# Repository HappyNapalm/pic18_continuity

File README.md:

# pic18_continuity
Repo for testing continuity

## TODO
* Hammer out the firmware.
* Set timer 3 up as the IO test timer. Make it 8 bits.
* Make footprint for push button.

##License
* Free for non commerical use.
* Remakes and spin offs must give credit to this project.

~Assemble boards to verify designs~

~Verify RJ45~

~Order Alpha Run~

~Get dimensions for DB9 connectors~

~Do battery footprint~

~Learn how to submit multiple boards in one design for vendor~

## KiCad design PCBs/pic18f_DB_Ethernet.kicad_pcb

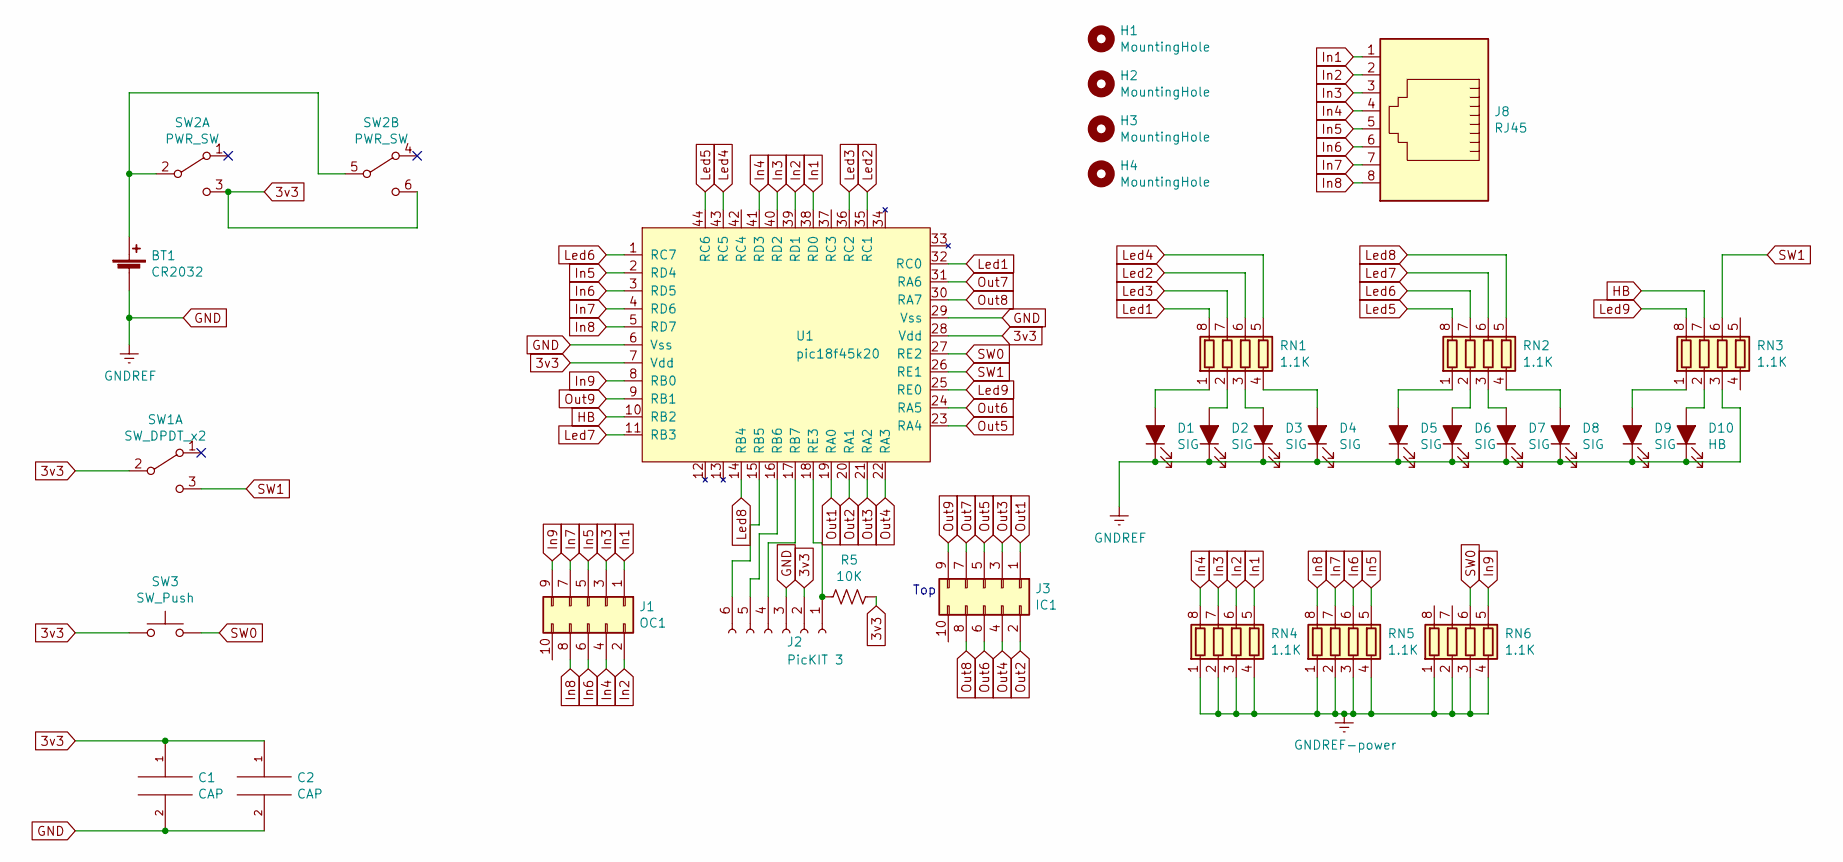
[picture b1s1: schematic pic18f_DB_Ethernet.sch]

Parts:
BT1: CR2032; BAT-HLD-001
C1, C2: CAP; C_0805_2012Metric
D1, D2, D3, D4, D5, D6, D7, D8, D9: SIG; LED_0603_1608Metric
D10: HB; LED_0603_1608Metric
H1, H2, H3, H4: MountingHole; MountingHole_3.2mm_M3
J1: OC1; PinHeader_2x05_P2.54mm_Vertical
J2: PicKIT 3; PinHeader_1x06_P2.54mm_Vertical
J3: IC1; PinHeader_2x05_P2.54mm_Vertical
J8: RJ45; RJ45_Amphenol_54602-x08_Horizontal
R5: 10K; R_0603_1608Metric
RN1, RN2, RN3, RN4, RN5, RN6: 1.1K; R_Array_Concave_4x0603
SW1: SW_DPDT_x2; JS202011SCQN
SW2: PWR_SW; JS202011SCQN
SW3: SW_Push; SPST_Button_FSM2JRT
U1: pic18f45k20; LQFP-44_10x10mm_P0.8mm

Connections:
3v3: C1.1, C2.1, J2.2, R5.1, SW1.2 (B), SW2.3 (C), SW2.6 (C), SW3.1, U1.7 (Vdd), U1.28 (Vdd)
HB: RN3.7 (R2.2), U1.10 (RB2)
In1: J1.1, J8.1, RN4.5 (R4.2), U1.38 (RD0)
In2: J1.2, J8.2, RN4.6 (R3.2), U1.39 (RD1)
In3: J1.3, J8.3, RN4.7 (R2.2), U1.40 (RD2)
In4: J1.4, J8.4, RN4.8 (R1.2), U1.41 (RD3)
In5: J1.5, J8.5, RN5.5 (R4.2), U1.2 (RD4)
In6: J1.6, J8.6, RN5.6 (R3.2), U1.3 (RD5)
In7: J1.7, J8.7, RN5.7 (R2.2), U1.4 (RD6)
In8: J1.8, J8.8, RN5.8 (R1.2), U1.5 (RD7)
In9: J1.9, RN6.5 (R4.2), U1.8 (RB0)
Led1: RN1.8 (R1.2), U1.32 (RC0)
Led2: RN1.6 (R3.2), U1.35 (RC1)
Led3: RN1.7 (R2.2), U1.36 (RC2)
Led4: RN1.5 (R4.2), U1.43 (RC5)
Led5: RN2.8 (R1.2), U1.44 (RC6)
Led6: RN2.7 (R2.2), U1.1 (RC7)
Led7: RN2.6 (R3.2), U1.11 (RB3)
Led8: RN2.5 (R4.2), U1.14 (RB4)
Led9: RN3.8 (R1.2), U1.25 (RE0)
unnamed: BT1.1 (+), SW2.2 (B), SW2.5 (B)
unnamed: D1.2 (A), RN1.1 (R1.1)
unnamed: D2.2 (A), RN1.2 (R2.1)
unnamed: D3.2 (A), RN1.3 (R3.1)
unnamed: D4.2 (A), RN1.4 (R4.1)
unnamed: D5.2 (A), RN2.1 (R1.1)
unnamed: D6.2 (A), RN2.2 (R2.1)
unnamed: D7.2 (A), RN2.3 (R3.1)
unnamed: D8.2 (A), RN2.4 (R4.1)
unnamed: D9.2 (A), RN3.1 (R1.1)
unnamed: D10.2 (A), RN3.2 (R2.1)
unnamed: J2.1, R5.2, U1.18 (RE3)
unnamed: J2.4, U1.17 (RB7)
unnamed: J2.5, U1.16 (RB6)
unnamed: J2.6, U1.15 (RB5)
Out1: J3.1, U1.19 (RA0)
Out2: J3.2, U1.20 (RA1)
Out3: J3.3, U1.21 (RA2)
Out4: J3.4, U1.22 (RA3)
Out5: J3.5, U1.23 (RA4)
Out6: J3.6, U1.24 (RA5)
Out7: J3.7, U1.31 (RA6)
Out8: J3.8, U1.30 (RA7)
Out9: J3.9, U1.9 (RB1)
SW0: RN6.6 (R3.2), SW3.2, U1.27 (RE2)
SW1: RN3.6 (R3.2), SW1.3 (C), U1.26 (RE1)

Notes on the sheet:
Top

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
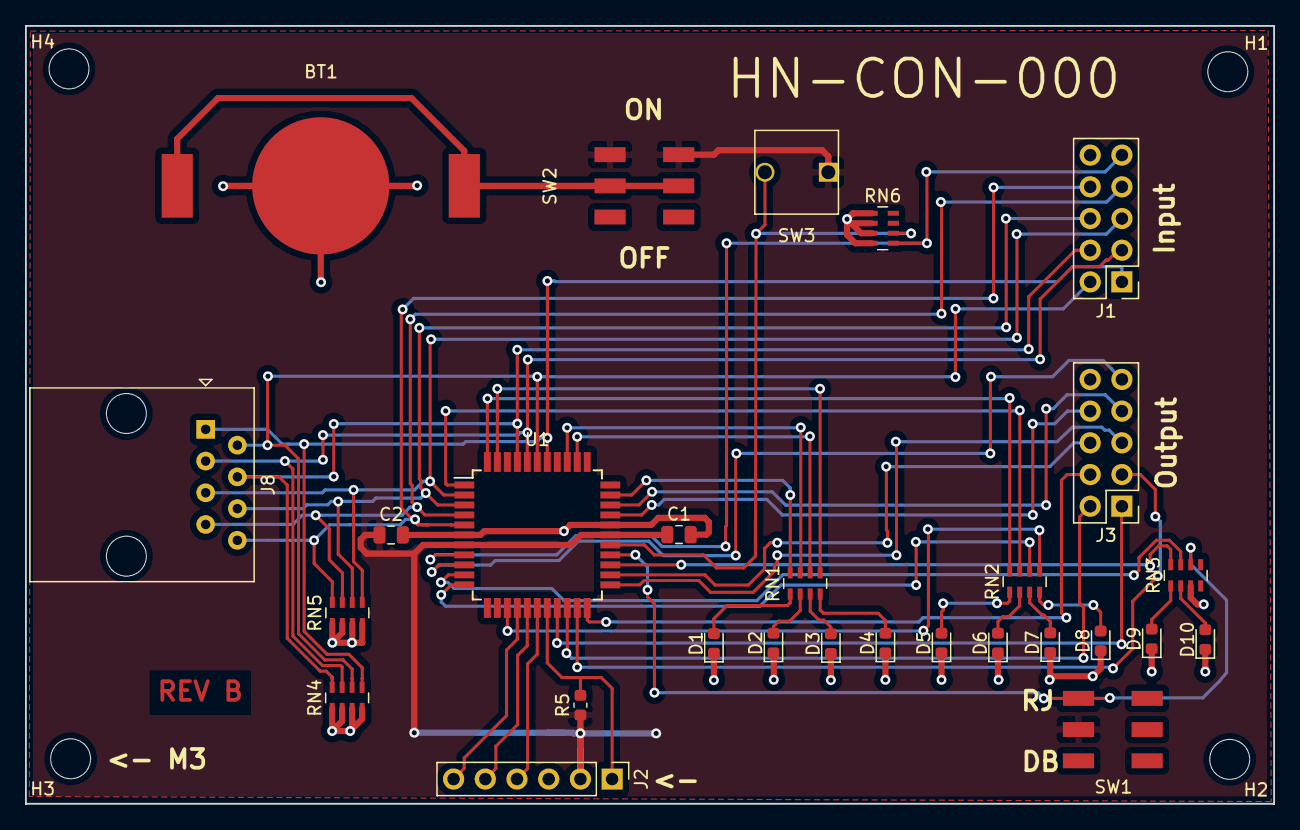
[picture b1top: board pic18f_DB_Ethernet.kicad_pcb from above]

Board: 2 copper layers, 100.0 x 62.3 mm, 32 parts (0 on the bottom side), 47 nets.

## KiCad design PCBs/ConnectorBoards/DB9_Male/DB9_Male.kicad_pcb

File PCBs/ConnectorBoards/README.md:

This dir is to contain the modular boards that the central board can connect to.

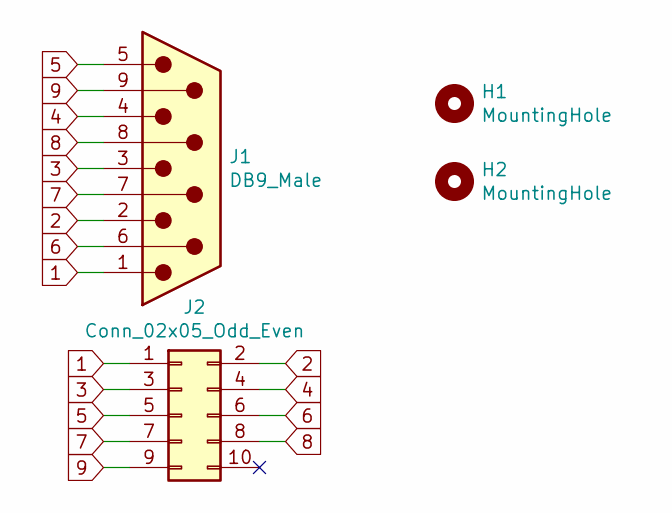
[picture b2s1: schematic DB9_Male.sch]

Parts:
H1, H2: MountingHole; MountingHole_3.2mm_M3
J1: DB9_Male; DSUB-9_Male_Horizontal_P2.77x2.84mm_EdgePinOffset4.94mm_Hou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
J2: Conn_02x05_Odd_Even; PinHeader_2x05_P2.54mm_Vertical

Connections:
1: J1.1, J2.1
2: J1.2, J2.2
3: J1.3, J2.3
4: J1.4, J2.4
5: J1.5, J2.5
6: J1.6, J2.6
7: J1.7, J2.7
8: J1.8, J2.8
9: J1.9, J2.9

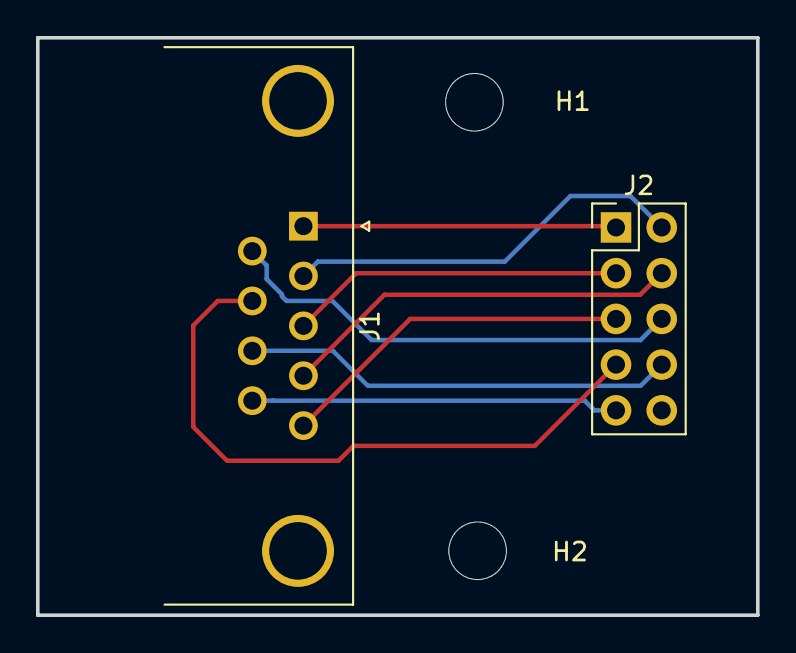
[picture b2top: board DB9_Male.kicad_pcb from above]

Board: 2 copper layers, 40.0 x 32.1 mm, 4 parts (0 on the bottom side), 9 nets.

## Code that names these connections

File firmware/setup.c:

#include <stdio.h>
//#include <stdlib.h>
#include <xc.h>
#include <htc.h>
#include "setup.h"
#include "leds.h"

//@About set GPIO table item to boolean
void set_IO (struct gstGPIO *IO, unsigned char item,unsigned char bValue)
{
    volatile unsigned char *ucLocal;
    ucLocal = IO[item].port;
    if (bValue)
    {
        *ucLocal |= (1 << IO[item].pin);
    }
    else
    {
        *ucLocal &= ~(1 << IO[item].pin);
    }
}

//@About get the state of an item from a GPIO table
unsigned char get_IO (struct gstGPIO *IO, unsigned char item)
{
    return (unsigned char)((*IO[item].port >> IO[item].pin) & 0x01);
}

struct gstGPIO astInputs[] = {
    {&PORTD, 0},
    {&PORTD, 1},
    {&PORTD, 2},
    {&PORTD, 3},
    {&PORTD, 4},
    {&PORTD, 5},
    {&PORTD, 6},
    {&PORTD, 7},
    {&PORTB, 0},
};

struct gstGPIO astOutputs[] = {
    {&LATA, 0},
    {&LATA, 1},
    {&LATA, 2},
    {&LATA, 3},
    {&LATA, 4},
    {&LATA, 5},
    {&LATA, 6},
    {&LATA, 7},
    {&LATB, 1},
};

void IO_setup (void)
{
  TRISA = 0x00;           //Outputs
  TRISC = 0x00;           //LEDS
  TRISBbits.RB0 = 1;      //In9
  TRISBbits.RB1 = 0;      //Out9
  TRISBbits.RB2 = 0;      //HB
  TRISBbits.RB3 = 0;      //LED7
  TRISBbits.RB4 = 0;      //LED8
  TRISD = 0xFF;           //Inputs
  TRISEbits.RE0 = 0;      //LED9
  TRISEbits.RE1 = 1;      //Switch 1A
  TRISEbits.RE2 = 1;      //Switch 1B
}


void Timer_and_Interrupt_setup (void)
{
    //Let this timer run as a free running timer
    
    //16 bits. 1:64 prescaler. Internal. 1 tick is 8us
    T0CON = 0b10010101;
    //INTCONbits.TMR0IE = 1;
    
    //8Mhz timer. Internal
    OSCCON = 0b01100111;
    
    
    T3CON = 0b00000101;
}

void clr_Timer (void)
{
    TMR0H = 0;
    TMR0L = 0;
}

void clr_Timer3 (void)
{
    TMR3H = 0;
    TMR3L = 0;
}

void __interrupt() ISR()
{
    if(TMR0IF)
    {
        TMR0IF = 0;
        clr_Timer();
        HB = !HB;
        gbTick++;
    }
    if(TMR3IF)
    {
        TMR3IF = 0;
        clr_Timer3();
        guc_3_Tick++;
        gucTestBit++;
    }
}

inline volatile unsigned short get_Time(void)
{
    return ((unsigned short)(TMR0H << 8) | TMR0L);
}

//@About: Checks with the free running timer
unsigned char bTimeUp(
                        unsigned short StartTime,
                        /*unsigned char StartOverFlowCount,*/
                        unsigned short Period
                     )
{
    unsigned char b = 0;
    unsigned short CurrentTime = get_Time();
    
    if (CurrentTime < StartTime)
    {
//        if(StartOverFlowCount > gbTick)
//        {
            if(((0xFFFF - StartTime) + CurrentTime) >= Period)
                {
                    b = 1;
                }
//        }
    }
    else if (CurrentTime - StartTime >= Period)
    {
        b = 1;
    }
    return b;
}

void setup(void)
{
    INTCONbits.GIE = 0;
    IO_setup();
    //clr_Timer();
    HB = 0;
    Timer_and_Interrupt_setup();
    INTCONbits.GIE = 1;
    INTCONbits.PEIE = 1;
    INTCONbits.TMR0IE = 1;
    T0CONbits.TMR0ON = 1;
    T3CONbits.TMR3ON = 0;
    all_LEDs();
    
    
}

#define HB_PERIOD 10000
void heartbeat(void)
{
    static unsigned char nbFirst;
    static unsigned short uwStartTime;
    static unsigned char ucOverFlow;
    //unsigned short uwCurrentTime = get_Time();
    if(!nbFirst)
    {
        uwStartTime = get_Time();
        ucOverFlow = gbTick;
        nbFirst = 1;
    }
    else
    {
        if(bTimeUp(uwStartTime,/*ucOverFlow,*/HB_PERIOD))
        {
            HB = !HB;
        }
    }
}

void compare_IO(unsigned char TargetBit)
{
    unsigned char bOutput = get_IO(astOutputs,TargetBit);
    unsigned char bInput  = get_IO(astInputs ,TargetBit);
    set_IO(astLEDs,TargetBit,(bOutput == bInput==1));
    
}

void testing(unsigned char TargetBit)
{
    static unsigned char b;
    static unsigned char ucLocalTicks;
    static unsigned char nbFirst;
    if(!nbFirst)
    {
        b = 1;
        nbFirst = 1;
        ucLocalTicks = guc_3_Tick;
        T3CONbits.TMR3ON = 1;   //Start the timer
    }
    if(ucLocalTicks != guc_3_Tick)
    {
        T3CONbits.TMR3ON = 0;
        b = 0;
        nbFirst = 0;
    }
    set_IO(astOutputs,TargetBit,b);
    compare_IO(TargetBit);
}

//# Potential EEPROM code below #//

// unsigned char read_eeprom(unsigned char ucAddress)
// {
//   unsigned char Data;
//   EEADR = ucAddress;       // Write The Address From Which We Wonna Get Data
//   EECON1bits.EEPGD = 0;  // Cleared To Point To EEPROM Not The Program Memory
//   EECON1bits.RD = 1;     // Start The Read Operation
//   Data = EEDATA;         // Read The Data
//   return (Data);

// }

// void write_eeprom(unsigned char ucAddress, unsigned char ucData)
// {
//   while(EECON1bits.WR);  // Waits Until Last Attempt To Write Is Finished
//   EEADR = ucAddress;       // Writes The Addres To Which We'll Wite Our Data
//   EEDATA = ucData;         // Write The Data To Be Saved
//   EECON1bits.EEPGD = 0;  // Cleared To Point To EEPROM Not The Program Memory
//   EECON1bits.WREN = 1;   // Enable The Operation !
//   INTCONbits.GIE = 0;    // Disable All Interrupts Untill Writting Data Is Done
//   EECON2 = 0x55;         // Part Of Writing Mechanism..
//   EECON2 = 0xAA;         // Part Of Writing Mechanism..
//   EECON1bits.WR = 1;     // Part Of Writing Mechanism..
//   INTCONbits.GIE = 1;    // Re-Enable Interrupts
//   EECON1bits.WREN = 0;   // Disable The Operation
//   EECON1bits.WR = 0;     // Ready For Next Writting Operation             
// }

// void reset_eeprom(void)
// {
//     unsigned char byte_count;
//     for(byte_count = 0; byte_count < 100; byte_count++)
//     {
//         write_eeprom(byte_count,0xff);
//     }
// }

// void HEX_2_LED(unsigned char EEPROM_MEM_ADDRESS)
// {
//     unsigned char LED_1;
//     unsigned char LED_2;
//     LED_1 = EEPROM_MEM_ADDRESS & 0x0F;
//     LED_2 = (EEPROM_MEM_ADDRESS & 0xF0 >> 4);
//     LED_Output_Single(LED_1,1);
//     LED_Output_Single(LED_2,1);
// }

// //On power up make it so you cycle through the EEPROM from 0-95 (six passes)
// //Read until you find one that mets the following criteria:
// //  (1) Not 0xFF
// //  (2) Highest value found
// //  (3) Then increment the value
// //  (4) Read the value and modulate by 16 to get the animation timer.
// //  (5) Assume that 0xFF at address 0 means we have restarted
// //  (6) If at address 95, then we can reset.


// void start_up(void)
// {
//     unsigned char ucDataOut = 0;
//     unsigned char ucValid = 0;
    
//     ucDataOut = read_eeprom(0x0A);
//     if(ucDataOut > 7)
//     {
//         ucDataOut = 0;
//     }
//     gucAnimationState = ucDataOut;
//     write_eeprom(0x0A,(ucDataOut+1));
// }

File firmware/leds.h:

/* 
 * File:   leds.h
 * Author: church
 *
 * Created on April 5, 2020, 5:24 PM
 */

#ifndef LEDS_H
#define	LEDS_H

#ifdef	__cplusplus
extern "C" {
#endif




#ifdef	__cplusplus
}
#endif

//Macros
#define LED1  LATCbits.LC0
#define LED2  LATCbits.LC2
#define LED3  LATCbits.LC1
#define LED4  LATCbits.LC5
#define LED5  LATCbits.LC6
#define LED6  LATCbits.LC7
#define LED7  LATBbits.LB3
#define LED8  LATBbits.LB4
#define LED9  LATEbits.LE0


//Global Vars
struct gstGPIO astLEDs[MAX_IO] = {
    { &LATC, 0 },  /*LED1*/
    { &LATC, 2 },  /*LED2*/
    { &LATC, 1 },  /*LED3*/
    { &LATC, 5 },  /*LED4*/
    { &LATC, 6 },  /*LED5*/
    { &LATC, 7 },  /*LED6*/
    { &LATB, 3 },  /*LED7*/
    { &LATB, 4 },  /*LED8*/
    { &LATE, 0 },  /*LED9*/
};
//extern const struct gstLEDs;

//Functions
extern void clr_LEDs (void);
extern void all_LEDs (void);
extern unsigned short get_LEDs (void);
extern void walk_LEDs (void);

#endif	/* SETUP_H */

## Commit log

2020-02-23 Initial KiCAD files
2020-02-23 made a pic18f symbol.
2020-02-23 TODO: Programming header. TODO: incorporate cabling design for connector modules.
2020-02-25 some basic connections laid down. TODO: double check I2C pins. Programming pins. And inputs.
2020-02-27 Finished basic schematic
2020-02-27 generated a basic net list
2020-02-27 generated basic todo list
2020-02-27 rough layout and part placement
2020-02-27 updated todo list
2020-02-29 Basic datasheets for the DB9 connectors
2020-02-29 Basic routing of known components complete. TODO: Outline, mouse bites, missing parts
2020-03-07 Added dpdt switch from stock. added battery clip. Reconsidering mouser bites. TODO: Orthagonal repo of parts rendered in KiCAD.
2020-03-10 Finished Rev A layout. Some research revealed that JLCPCB does not support what I want. I might just send the break out into a different pcb.
2020-03-10 Restructed project
2020-03-10 markdown edit
2020-03-13 Minor rerouting to address power trace width. Added OSHW logo. Updated todo list
2020-03-15 changed RJ45 jack to unsheilded. Printed main board gerbers and gerber pdfs
2020-03-15 generated the male pcbs
2020-03-31 rough idea of code
2020-03-31 Noodling through basic designs. TODO assemble and document boards
2020-03-31 Formalized TODO list
    Summarized commit comments into TODO list.
2020-04-03 chipping away at design
2020-04-05 Added Microchip proj to the repo. Cleaned some psuedo code away
2020-04-05 Editted code
2020-04-08 Made some progress generalizing the IO space.
2020-04-09 working on unifying my IO space. Saving work.
2020-04-15 saving progress
2020-04-17 Saving progress. Reused Flash LEDS as a jog through all the LEDs. TODO: Make an LED breakout board for testing IO. Note: I am eating through battery much faster than expected. Consider introducing po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
2020-04-17 Hammered the interrupts. Rough FRT working. Time to refine and add some defensive programming.
2020-04-18 Debugging the FRT. Bugs were found.
2020-04-18 Making a branch of the software without the free running timer.
2020-04-23 Working on the IO routines. (Probably missing pull down resistors. Will need to make a test board to verify hardware.) TODO configure processor to make debugging easier.
2020-04-23 Input table was built from the Latch addresses, not the port address.
2020-04-23 Issue discovered with IO testing. Further debug required.
2020-05-18 addressing hardware problems on PCB design. Pull downs missing and while a breakout works for prototyping code, it is time to commit the changes in FR4.
2020-05-18 Updated todo list in the readme. Need to make button footprint.
2020-05-19 Finished REV B design.
2020-07-04 Submitted gerbers to JLCPCB
